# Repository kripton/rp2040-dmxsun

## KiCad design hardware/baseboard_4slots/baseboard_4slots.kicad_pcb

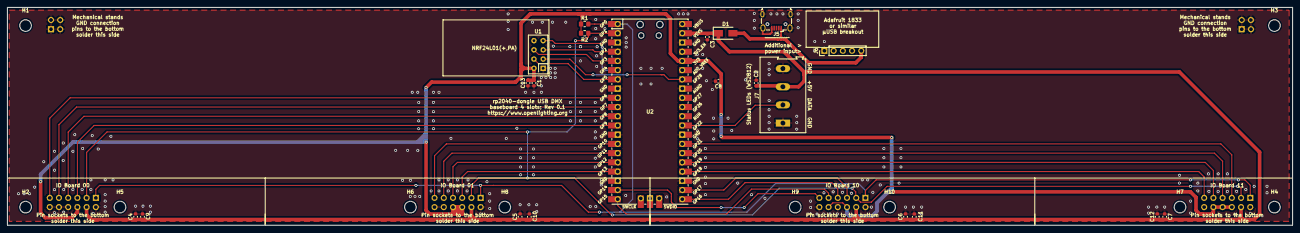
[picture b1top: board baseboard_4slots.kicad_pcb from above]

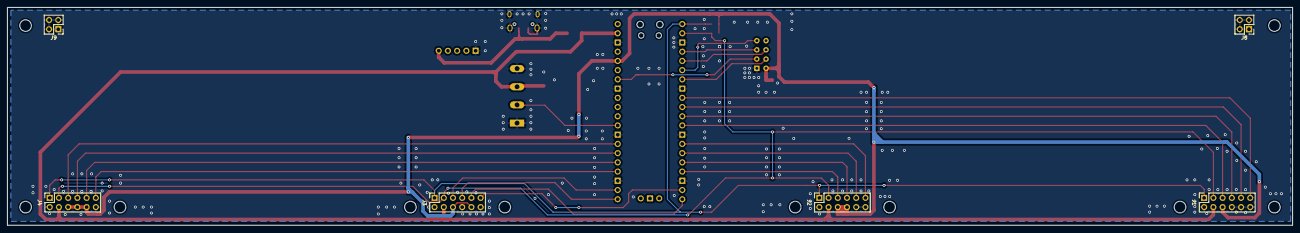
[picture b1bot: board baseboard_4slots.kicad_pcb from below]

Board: 2 copper layers, 354.0 x 60.0 mm, 37 parts (6 on the bottom side), 28 nets.

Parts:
C1, C2, C3, C4, C5, C6, C7, C8: 100nF; C_0603_1608Metric
C9, C10, C11, C12, C13: 1nF; C_0603_1608Metric
D1: SS14; D_SMA
H1, H2, H3, H4, H5, H6, H7, H8, H9, H10: MountingHole; MountingHole_3.2mm_M3
J1: IO-Board_00; PinSocket_2x06_P2.54mm_Vertical
J2: IO-Board_01; PinSocket_2x06_P2.54mm_Vertical
J3: IO-Board_10; PinSocket_2x06_P2.54mm_Vertical
J4: IO-Board_11; PinSocket_2x06_P2.54mm_Vertical
J5: USB_B_Micro; USB_Micro-B_Wuerth_629105150521
J6: Conn_01x05: Adafruit 1833; PinHeader_1x05_P2.54mm_Vertical
J7: Screw_Terminal_01x04; TerminalBlock_Altech_AK300-4_P5.00mm
J8, J9: Conn_02x02_Odd_Even; PinHeader_2x02_P2.54mm_Vertical
R1, R2: 2k; R_0805_2012Metric_Pad1.20x1.40mm_HandSolder
U1: NRF24L01_Breakout; nRF24L01_Breakout
U2: Pico; RPi_Pico_SMD_TH

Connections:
+3V3: C1.1, C8.1, C13.1, J1.6, J2.6, J2.8, J3.6, J3.10, J4.6, J4.8, J4.10, R1.1, R2.1, U1.2, U2.36
/IO0_GP0: J1.11, U2.9
/IO0_GP1: J1.9, U2.10
/IO0_GP2: J1.7, U2.11
/IO0_GP3: J1.5, U2.12
/IO1_GP0: J2.11, U2.14
/IO1_GP1: J2.9, U2.15
/IO1_GP2: J2.7, U2.16
/IO1_GP3: J2.5, U2.17
/IO2_GP0: J3.11, U2.19
/IO2_GP1: J3.9, U2.20
/IO2_GP2: J3.7, U2.21
/IO2_GP3: J3.5, U2.22
/IO3_GP0: J4.11, U2.24
/IO3_GP1: J4.9, U2.25
/IO3_GP2: J4.7, U2.26
/IO3_GP3: J4.5, U2.27
/NRF_CE: U1.3, U2.34
/SCL: J1.3, J2.3, J3.3, J4.3, R2.2, U2.2
/SDA: J1.1, J2.1, J3.1, J4.1, R1.2, U2.1
/SPI_CLK: U1.5, U2.4
/SPI_CS0: U1.4, U2.7
/SPI_MISO: U1.7, U2.6
/SPI_MOSI: U1.6, U2.5
/STATUS_LEDS: J7.2, U2.29
GND: C1.2, C2.2, C3.2, C4.2, C5.2, C6.2, C7.2, C8.2, C9.2, C10.2, C11.2, C12.2, C13.2, J1.2, J1.8, J1.10, J1.12, J2.2, J2.10, J2.12, J3.2, J3.8, J3.12, J4.2, J4.12, J5.5, J5.6, J6.1, J7.1, J7.4, J8.1, J8.2, J8.3, J8.4, J9.1, J9.2, J9.3, J9.4, U1.1, U2.3, U2.8, U2.13, U2.18, U2.23, U2.28, U2.33, U2.38
unnamed: D1.2, J5.1, J6.5
VDD: C2.1, C3.1, C4.1, C5.1, C6.1, C7.1, C9.1, C10.1, C11.1, C12.1, D1.1, J1.4, J2.4, J3.4, J4.4, J7.3, U2.39

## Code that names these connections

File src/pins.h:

// GPIO pins used by the rp2040-dmxsun
// GPIO numbers of the RP2040 chip,
// NOT hardware pin numbers of the pico module!
// All in one file for easy reference

#include <bsp/board.h>          // On-board-LED

// I2C to IO boards for detection and configuration
// (Every IO board has one 2048kbit EEPROM)
#define PIN_I2C_SCL     0
#define PIN_I2C_SDA     1

// SPI to the optional nRF24L01+ module
#define PIN_SPI_CLK     2
#define PIN_SPI_MOSI    3
#define PIN_SPI_MISO    4
#define PIN_SPI_CS0     5
#define PIN_RF24_CE    28

// SPI to the option W5500 SPI Ethernet module
#define PIN_SPI_CS_W   26
#define PIN_IRQ_W5500  27

// IO board 00
#define PIN_IO00_0      6
#define PIN_IO00_1      7
#define PIN_IO00_2      8
#define PIN_IO00_3      9

// IO board 01
#define PIN_IO01_0     10
#define PIN_IO01_1     11
#define PIN_IO01_2     12
#define PIN_IO01_3     13

// IO board 10
#define PIN_IO10_0     14
#define PIN_IO10_1     15
#define PIN_IO10_2     16
#define PIN_IO10_3     17

// IO board 11
#define PIN_IO11_0     18
#define PIN_IO11_1     19
#define PIN_IO11_2     20
#define PIN_IO11_3     21

// Pico's on-board, single-color status LED
// If a regular "Pico" is detected at runtime => Port 25
// If a Pico-W is detected at runtime => GPIO 0 of the cyw43
#define PIN_LED_PICO   25
#define PIN_LED_PICOW  CYW43_WL_GPIO_LED_PIN

// WS2812-based status LEDs
#define PIN_LEDS       22

// Helper pin for DMX TX (DriverEnable output)
// this is mainly useful to trigger an oscilloscope to check the
// generated DMX frames
#define PIN_TRIGGER    26

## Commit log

2021-03-04 Just a small test to see if C++ can be used sanely on the RP2040 and the toolchain in GH Actions works as well as mine
2021-03-04 Make getLogBuffer actually return the size of what was output
2021-03-30 Add RF24 as git submodule
2021-03-30 Compile the RF24 library
2021-03-30 Add skeleton files for wireless comms
2021-03-30 Proper gcc 10 fix: Move global data to main.c and declare them with extern keyword where required
2021-03-30 Logging improvements. This is getting useful :)
2021-03-30 WiP: Try to get an nRF24 module running
2021-04-01 RF24 progress: Radio seem to be working
2021-04-01 Rename RF24/utility/RPi-Pico -> RF24/utility/rp2 and remove unneeded header includes
2021-04-06 WiP: RF24 development and proofing
2021-04-07 WiP: Working solution to transmit 16 DMX channels via the nRF24 module :D
2021-04-09 Wireless DMX is working :D Decrease the sending interval to 10 times per second
2021-04-09 Transmit 24 byte of payload, increase SPI speed to default (= 10MHz) and include RF24Network and RF24Mesh
2021-04-10 WiP: Include RF24 library by my proposal of its CMakeLists.txt file. Doesn't compile yet since RF24Network would need an equivalent to make RF24Mesh happy
2021-04-11 Move the RF24 from src/ to new lib/ folder and update to latest changes
2021-04-11 Also move RF24Network and RF24Mesh to lib folder. Adapt cmake file to new location of RF24/CMakeLists.txt
2021-04-11 Include RF24, RF24Network and RF24Mesh by using their CMakeLists.txt files (that currently exist only in my kripton-rp2xxx branches)
2021-04-11 Define SPI pins and RF24Network options in the cmake file
2021-04-11 Also add the mesh config to CMakeLists.txt and re-format that file a little
2021-04-11 Add heatshrink data compression library as submodule
2021-04-11 CMakeLists: Some more comments and restructuring
2021-04-17 Revert to normal, slow LED blinking and rmeove debugging output for now
2021-04-17 Change all submodule URLs to point to my clones. For now :)
2021-04-17 Let RF24Mesh and RF24Network submodules point to a commit on branch kripton-rp2xxx so the CMakeLists.txt files are there
2021-04-17 Checkout or own repo with submodules and update pico-sdk to v1.1.2
2021-04-17 Compile in the heatshrink library
2021-04-17 Configure the heatshrink library with the parameters best for DMX512 packages
2021-04-18 Implement basic IO board scanning (= EEPROM reading) via I2C bus
2021-04-19 Enligthen the status LEDs
2021-04-20 Allow resetting via UDB CDC baud rate changes
2021-06-20 Add picojson library
2021-12-22 Wireless mesh: Ping nodes periodically and add them to the wireless stats
2021-12-22 Start implementing mesh code and wireless stats
2021-12-22 WiP: Debug cross-library interrupt problems ...
2021-12-22 Rename PIO program tx16 to tx_dmx and make it have a flexible amount of IOs
2021-12-22 WiP: Move our own DMX data generation code from PIO0, SM0, DMA_IRQ0 to PIO1, SM2, DMA_IRQ1 so we don't clash with Pico-DMX' DmxInput-code
2021-12-22 Introduce a new DebugStruct that we can access via the web server (for stuff that happens too often to log it) and make our local DMX generation a shared IRC handler instead of an exclusive one
2021-12-22 Prepare for DMX input: Add PIO program and rewrite DMA-IRQ-handler
2021-12-22 WiP: Inline DMX RX
2021-12-22 Move localdmx TX to PIO 1, SM 2 so we have PIO 0 for DMX inputs
2021-12-22 Typo and one comment
2021-12-22 Debugging using onboard-LED and debugStruct
2021-12-22 Replace our critical_section bufferLock with a mutex so that incoming and ready DMX data can interrupt us while the MultiUniverseOut waveform is being generated. Otherwise, a frame would be lost
2021-12-22 Make LED patterns on last LED compatible with input blinking. And temporarily copy DMX data from first input to Local buffer 0
2021-12-22 Pico-DMX: Update commit hash
2021-12-22 Define a fixed pin for debugging
2021-12-22 Dmx input: Use one of the status LEDs to show that DMX in data is detected
2021-12-22 WiP: Prepare port management and port direction switching
2021-12-22 Update Pico-DMX library so input can read all channels
2021-12-22 Update Pico-DMX to v3.0.0 (= upstream main) since all of my PRs have been merged 🥳
2021-12-22 Re-enable the status LED task that was disabled for debugging but accidentially committed
2021-12-22 LocalDMX: Prepare for start codes != 0. And some refactoring around the PIOs and SMs
2021-12-22 Add Pico-DMX library via submodule
2021-12-22 Update Pico-DMX for reliability improvment
2021-12-22 Only start sending a frame if no other is being sent
2021-12-22 Only send DMX frames if the data changes. Used for debugging DMX input
2022-01-09 Bump nerdyscout/kicad-exports from 2.2 to 2.3.1
    Bumps [nerdyscout/kicad-exports](https://github.com/nerdyscout/kicad-exports) from 2.2 to 2.3.1.
    - [Release notes](https://github.com/nerdyscout/kicad-exports/releases)
    - [Changelog](https://github.com/nerdyscout/kicad-exports/blob/main/CHANGELOG.md)
    - [Commits](https://github.com/nerdyscout/kicad-exports/compare/v2.2...v2.3.1)
    ---
    updated-dependencies:
2022-01-09 Bump react-chartjs-2 from 3.3.0 to 4.0.0 in /wwwsrc
    Bumps [react-chartjs-2](https://github.com/reactchartjs/react-chartjs-2) from 3.3.0 to 4.0.0.
    - [Release notes](https://github.com/reactchartjs/react-chartjs-2/releases)
    - [Changelog](https://github.com/reactchartjs/react-chartjs-2/blob/master/CHANGELOG.md)
    - [Commits](https://github.com/reactchartjs/react-chartjs-2/compare/v3.3.0...v4.0.0)
    ---
    updated-dependencies:
2022-01-09 Bump react-router-dom from 5.3.0 to 6.2.1 in /wwwsrc
    Bumps [react-router-dom](https://github.com/remix-run/react-router/tree/HEAD/packages/react-router-dom) from 5.3.0 to 6.2.1.
    - [Release notes](https://github.com/remix-run/react-router/releases)
    - [Commits](https://github.com/remix-run/react-router/commits/v6.2.1/packages/react-router-dom)
    ---
    updated-dependencies:
    - dependency-name: react-router-dom
2022-01-09 Bump react-scripts from 4.0.3 to 5.0.0 in /wwwsrc
    Bumps [react-scripts](https://github.com/facebook/create-react-app/tree/HEAD/packages/react-scripts) from 4.0.3 to 5.0.0.
    - [Release notes](https://github.com/facebook/create-react-app/releases)
    - [Changelog](https://github.com/facebook/create-react-app/blob/main/CHANGELOG.md)
    - [Commits](https://github.com/facebook/create-react-app/commits/react-scripts@5.0.0/packages/react-scripts)
    ---
    updated-dependencies:
2022-01-19 Ignore auto-generated fsdata.c and don't EXTRACT_ALL so doxygen tells us what docu is missing
2022-01-19 First steps adding doxygen
2022-01-19 Make the doxygen results a little nicer
2022-01-19 Wow, doxygen can use our README.md as the main page. However, the content is a bit broken after the images ...
2022-01-24 Document pins.h, StatusLeds and BoardConfig classes (yet excluding members)
2022-01-24 Document DmxBuffer class as well
2022-01-24 Document EDP class
2022-01-24 Add @file to all headers so references work and the source can be browsed
2022-03-02 Bump actions/checkout from 2 to 3
    Bumps [actions/checkout](https://github.com/actions/checkout) from 2 to 3.
    - [Release notes](https://github.com/actions/checkout/releases)
    - [Changelog](https://github.com/actions/checkout/blob/main/CHANGELOG.md)
    - [Commits](https://github.com/actions/checkout/compare/v2...v3)
    ---
    updated-dependencies:
2022-04-11 Bump actions/upload-artifact from 2 to 3
    Bumps [actions/upload-artifact](https://github.com/actions/upload-artifact) from 2 to 3.
    - [Release notes](https://github.com/actions/upload-artifact/releases)
    - [Commits](https://github.com/actions/upload-artifact/compare/v2...v3)
    ---
    updated-dependencies:
    - dependency-name: actions/upload-artifact
2022-06-20 Try direct differential mode (see https://github.com/jostlowe/Pico-DMX/issues/27)
2022-06-22 Hopefully fix the generation by separating the bitoffsets
2022-06-22 Bump snappyjs from 0.6.1 to 0.7.0 in /wwwsrc
    Bumps [snappyjs](https://github.com/zhipeng-jia/snappyjs) from 0.6.1 to 0.7.0.
    - [Release notes](https://github.com/zhipeng-jia/snappyjs/releases)
    - [Commits](https://github.com/zhipeng-jia/snappyjs/compare/v0.6.1...v0.7.0)
    ---
    updated-dependencies:
    - dependency-name: snappyjs
2022-06-26 Prepare integration of the ENC28J60 ethernet module
2022-06-26 Make pinging the device via the ENC28J60 work
2022-06-27 Make RXing multiple ArtNet-universes via the ENC28J60 actually work
2022-06-27 Use a queue_t also for the tusb network stack
2022-07-04 Minimal trace routing improvements
2022-07-04 Required changes for SPI bus sharing in pico-enc28j60 library
2022-07-25 Add FreeRTOS-Kernel submodule
2022-07-25 Include FreeRTOS kernel in the compilation and link it as library
2022-07-25 Hack it together so it works very roughly with FreeRTOS
2022-07-27 Fix tasks so they actually work
2022-07-28 Switch to smp branch of FreeRTOS so we actually use both cores
2022-07-28 Re-enable wireless, add core affinity and tune priorities and stack sizes so that at least the web server works again
2022-11-15 Bump nerdyscout/kicad-exports from 2.2 to 2.3
    Bumps [nerdyscout/kicad-exports](https://github.com/nerdyscout/kicad-exports) from 2.2 to 2.3.
    - [Release notes](https://github.com/nerdyscout/kicad-exports/releases)
    - [Changelog](https://github.com/nerdyscout/kicad-exports/blob/main/CHANGELOG.md)
    - [Commits](https://github.com/nerdyscout/kicad-exports/compare/v2.2...v2.3)
    ---
    updated-dependencies:
2022-11-17 Bump react-chartjs-2 from 4.3.1 to 5.0.0 in /wwwsrc
    Bumps [react-chartjs-2](https://github.com/reactchartjs/react-chartjs-2) from 4.3.1 to 5.0.0.
    - [Release notes](https://github.com/reactchartjs/react-chartjs-2/releases)
    - [Changelog](https://github.com/reactchartjs/react-chartjs-2/blob/master/CHANGELOG.md)
    - [Commits](https://github.com/reactchartjs/react-chartjs-2/compare/v4.3.1...v5.0.0)
    ---
    updated-dependencies:
2024-11-03 Add initial, untested implementation of Ethernet via W5500 chip / Wiz850 module
2024-11-03 Switch W5500 from spi1 to spi0. No wonder it didn't work ;)
2024-11-03 Add W5500MacRaw library to talk to W5500 chips and use them with lwIP
2024-11-03 Update lwIP and adjust buffer size in one call to W5500 driver
2024-11-04 Try fixing the W5500 issues
